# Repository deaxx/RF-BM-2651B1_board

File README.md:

# RF-BM-2651B1_board
RF-BM-2651B1_board

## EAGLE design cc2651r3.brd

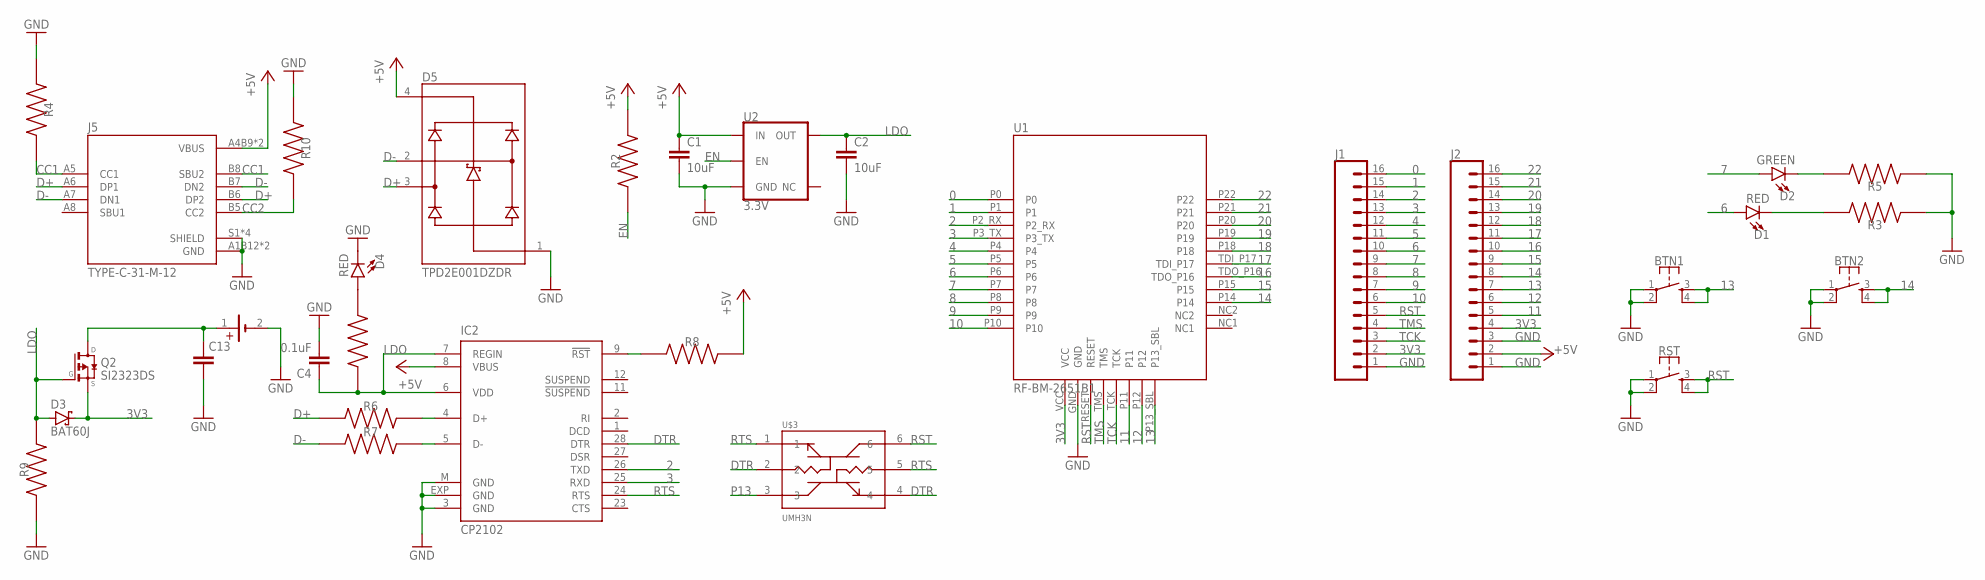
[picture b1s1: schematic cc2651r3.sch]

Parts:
BT2: 79527141
BTN1, BTN2: MOMENTARY-SWITCH-SPST-2-SMD-4.6X2.8MM; TACTILE_SWITCH_SMD_4.6X2.8MM
C1, C2: 10uF; 0603
C4: 0.1uF; 0603
C13: C_TANTALUM-2917(7343-METRIC); CAPM7343X310
D1, D4: RED; LED-0603
D2: GREEN; LED-0603
D3: BAT60J; SOD323_ST
D5: TPD2E001DZDR; SOT192P237X122-4N
IC2: CP2102; MLP28
J1, J2: CONN_161X16_NO_SILK; 1X16_NO_SILK
J5: TYPE-C-31-M-12; HRO_TYPE-C-31-M-12
Q2: SI2323DS; SOT23
R2, R3, R4, R5, R6, R7, R8, R9, R10, R11: RC0402FR-073M6L; RESC1005X40N
RST: MOMENTARY-SWITCH-SPST-2-SMD-4.6X2.8MM; TACTILE_SWITCH_SMD_4.6X2.8MM
U1: RF-BM-2651B1
U2: 3.3V; SOT23-5
U$3: UMH3N; SOP65P210X100-6N

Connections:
0: J1.16, U1.P0
1: J1.15, U1.P1
2: IC2.26 (TXD), J1.14, U1.P2_RX
3: IC2.25 (RXD), J1.13, U1.P3_TX
3V3: D3.C, J1.2, J2.4, Q2.2 (S), U1.VCC
4: J1.12, U1.P4
5: J1.11, U1.P5
6: D1.A, J1.10, U1.P6
7: D2.A, J1.9, U1.P7
8: J1.8, U1.P8
9: J1.7, U1.P9
10: J1.6, U1.P10
11: J2.5, U1.P11
12: J2.6, U1.P12
13: BTN1.3, BTN1.4, J2.7, U1.P13_SBL
14: BTN2.3, BTN2.4, J2.8, U1.P14
15: J2.9, U1.P15
16: J2.10, U1.TDO_P16
17: J2.11, U1.TDI_P17
18: J2.12, U1.P18
19: J2.13, U1.P19
20: J2.14, U1.P20
21: J2.15, U1.P21
22: J2.16, U1.P22
+5V: C1.1, D5.4 (VCC), IC2.8 (VBUS), J2.2, J5.A4B9 (VBUS), J5.B4A9 (VBUS), R2.2, R8.2, U2.1 (IN)
CC1: J5.A5 (CC1), J5.B8 (SBU2), R4.2
CC2: J5.B5 (CC2), R10.2
D+: D5.3 (IO2), J5.A6 (DP1), J5.B6 (DP2), R6.1
D-: D5.2 (IO1), J5.A7 (DN1), J5.B7 (DN2), R7.1
DTR: IC2.28 (DTR), U$3.2, U$3.4
EN: R2.1, U2.3 (EN)
GND: BT2.2 (-), BTN1.1, BTN1.2, BTN2.1, BTN2.2, C1.2, C2.2, C4.2, C13.2, D4.C, D5.1 (GND), IC2.3 (GND), IC2.EXP (GND), IC2.M (GND), J1.1, J2.1, J2.3, J5.A1B12 (GND), J5.B1A12 (GND), J5.S1 (SHIELD), J5.S2 (SHIELD), J5.S3 (SHIELD), J5.S4 (SHIELD), R3.1, R4.1, R5.1, R9.1, R10.1, RST.1, RST.2, U1.GND, U2.2 (GND)
LDO: C2.1, C4.1, D3.A, IC2.6 (VDD), IC2.7 (REGIN), Q2.1 (G), R9.2, R11.2, U2.5 (OUT)
unnamed: IC2.9 (!RST), R8.1
unnamed: D1.C, R3.2
unnamed: D2.C, R5.2
unnamed: IC2.4 (D+), R6.2
unnamed: IC2.5 (D-), R7.2
unnamed: BT2.1 (+), C13.1, Q2.3 (D)
unnamed: D4.A, R11.1
P13: U$3.3
RST: J1.5, RST.3, RST.4, U1.RESET, U$3.6
RTS: IC2.24 (RTS), U$3.1, U$3.5
TCK: J1.3, U1.TCK
TMS: J1.4, U1.TMS

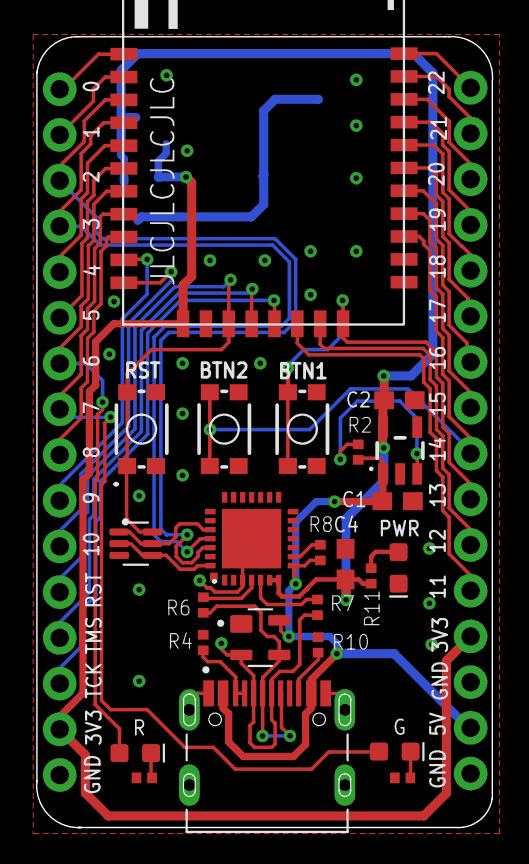
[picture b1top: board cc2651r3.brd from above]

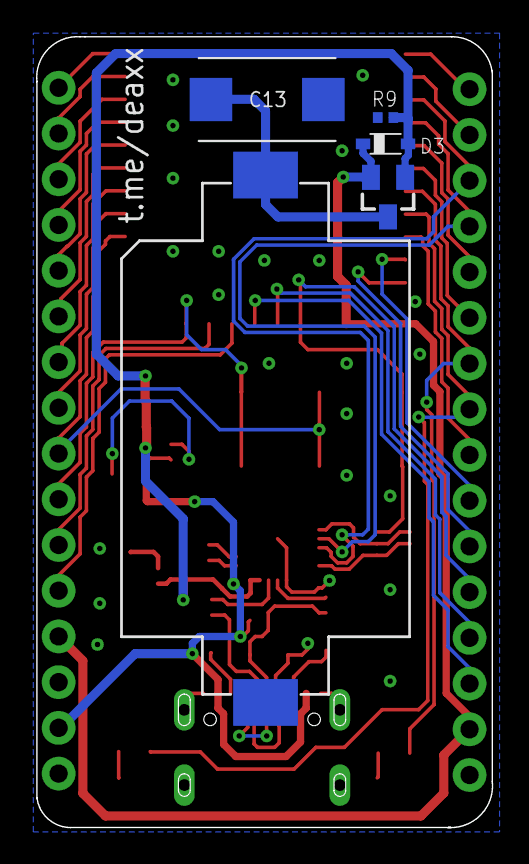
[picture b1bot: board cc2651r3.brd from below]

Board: 4 copper layers, 25.3 x 43.9 mm, 31 parts (5 on the bottom side), 44 nets.

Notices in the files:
parts and their libraries:
SparkFun-Connectors: Licensing: Creative Commons ShareAlike 4.0 International - https://creativecommons.org/licenses/by-sa/4.0
